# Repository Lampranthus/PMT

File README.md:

NOTAS
---
PCB

El adc tiene que llevar la siguiente configuración, solo se tenecesita por ahora un solo canal.

en esta configuración se utiliza la referencia programable del adc, con ese valor de resistencias la referncia se cambia a 1.5V segun la hora de datos.

Mientras que para recibir la señal senecesita esta configuración, solo se necesita por ahora un solo canal.

---
FPGA

QUiero usar por el momoento la DE2-115 ya que cuenta con conexiones Ethernet, voy a conectar la pcb los pines de la fpga con un socket, por el monento imagino que será mejor hacer la pcb de manera vertical respecto a la fpga, ya que por el estacio parece lo mejor.

tanbien se tienen que agregar 2 pines a la pcb de start y stop, los cuales se agregarán pero aun tengo la duda su puedo utilizar otra pcb que tengo donde utilizo el puerto hsmc de la fpga y 2 comparadores para recibir 2 señales, pero por el momento agregaré todo a una sola pcb.

---

Logré hacer una conectar la pgfa a mi laptop a 1gbs con el ejemplo de web server ahora toca cofigurar el ejemplo para loso usar la comunicación.

---

Para no depender del nios2 estoy optando por utilizar el verilog-ethernet

https://github.com/alexforencich/verilog-ethernet

ya hice que funcionara el echo por lo que ahora falta modificarlo para hacer la pruebas de envio de datos de la fpga a la laptop y hacer que la computadora guarde estos datos.

---

Estos son los pasos para utilizar ese repositorio primero vas al ejemplo de la de2-115 ejecutas el siguiente comando para generar los archivos,

```bash
make
```
luego para configurar la fpga se ejecuta el siguiente comando,

```bash
make program
```
Dado que la FPGA no tiene servidor DHCP, tu PC necesita una IP fija.

```bash
sudo ip addr flush dev enxc8a362c9957b
sudo ip addr add 192.168.1.100/24 dev enxc8a362c9957b
sudo ip link set enxc8a362c9957b up
```
Reemplaza enxc8a362c9957b con el nombre real de tu interfaz Ethernet (usa ip addr para comprobar).

Ejecuntando esos comando ya se puede recibir el echo desde la fpga utilizando el comando,

```bash
echo "respuesta" | nc -u 192.168.1.128 1234
```
Cuando haces eso, netcat:

1. Abre un socket UDP.

2. Envía el mensaje a la FPGA.

3. Se queda esperando brevemente una respuesta en el mismo socket (puerto efímero).

4. Recibe la respuesta de la FPGA (que hizo eco del mensaje) y lo imprime.

5. Luego cierra el socket.

Y sí, cuando el socket no recibe más datos, tienes que presionar Ctrl+C para cerrarlo porque nc no se cierra automáticamente si está esperando más datos.

---
En el repositorio hay un codigo en python que funciona para neciar cierto numero de paquestes a la fpga y cuando esta los regrese cuenta cuantos de estos paquestes se perdieron en el loop, hice una prueba con 100 millones de packetes y el porcentaje de paquetes que se perdieron fue minima por lo que alparecer los datos dificilmente se pierden.

ahora faltaría ver la velocidad en la que los datos se envian.

---
estoy utilizando el protocolo udp, y haciendo una prueba para el limite de longitud antes de que el ejemplo de echo no respondiera llegue a 1472 bytes de payload limite.

---

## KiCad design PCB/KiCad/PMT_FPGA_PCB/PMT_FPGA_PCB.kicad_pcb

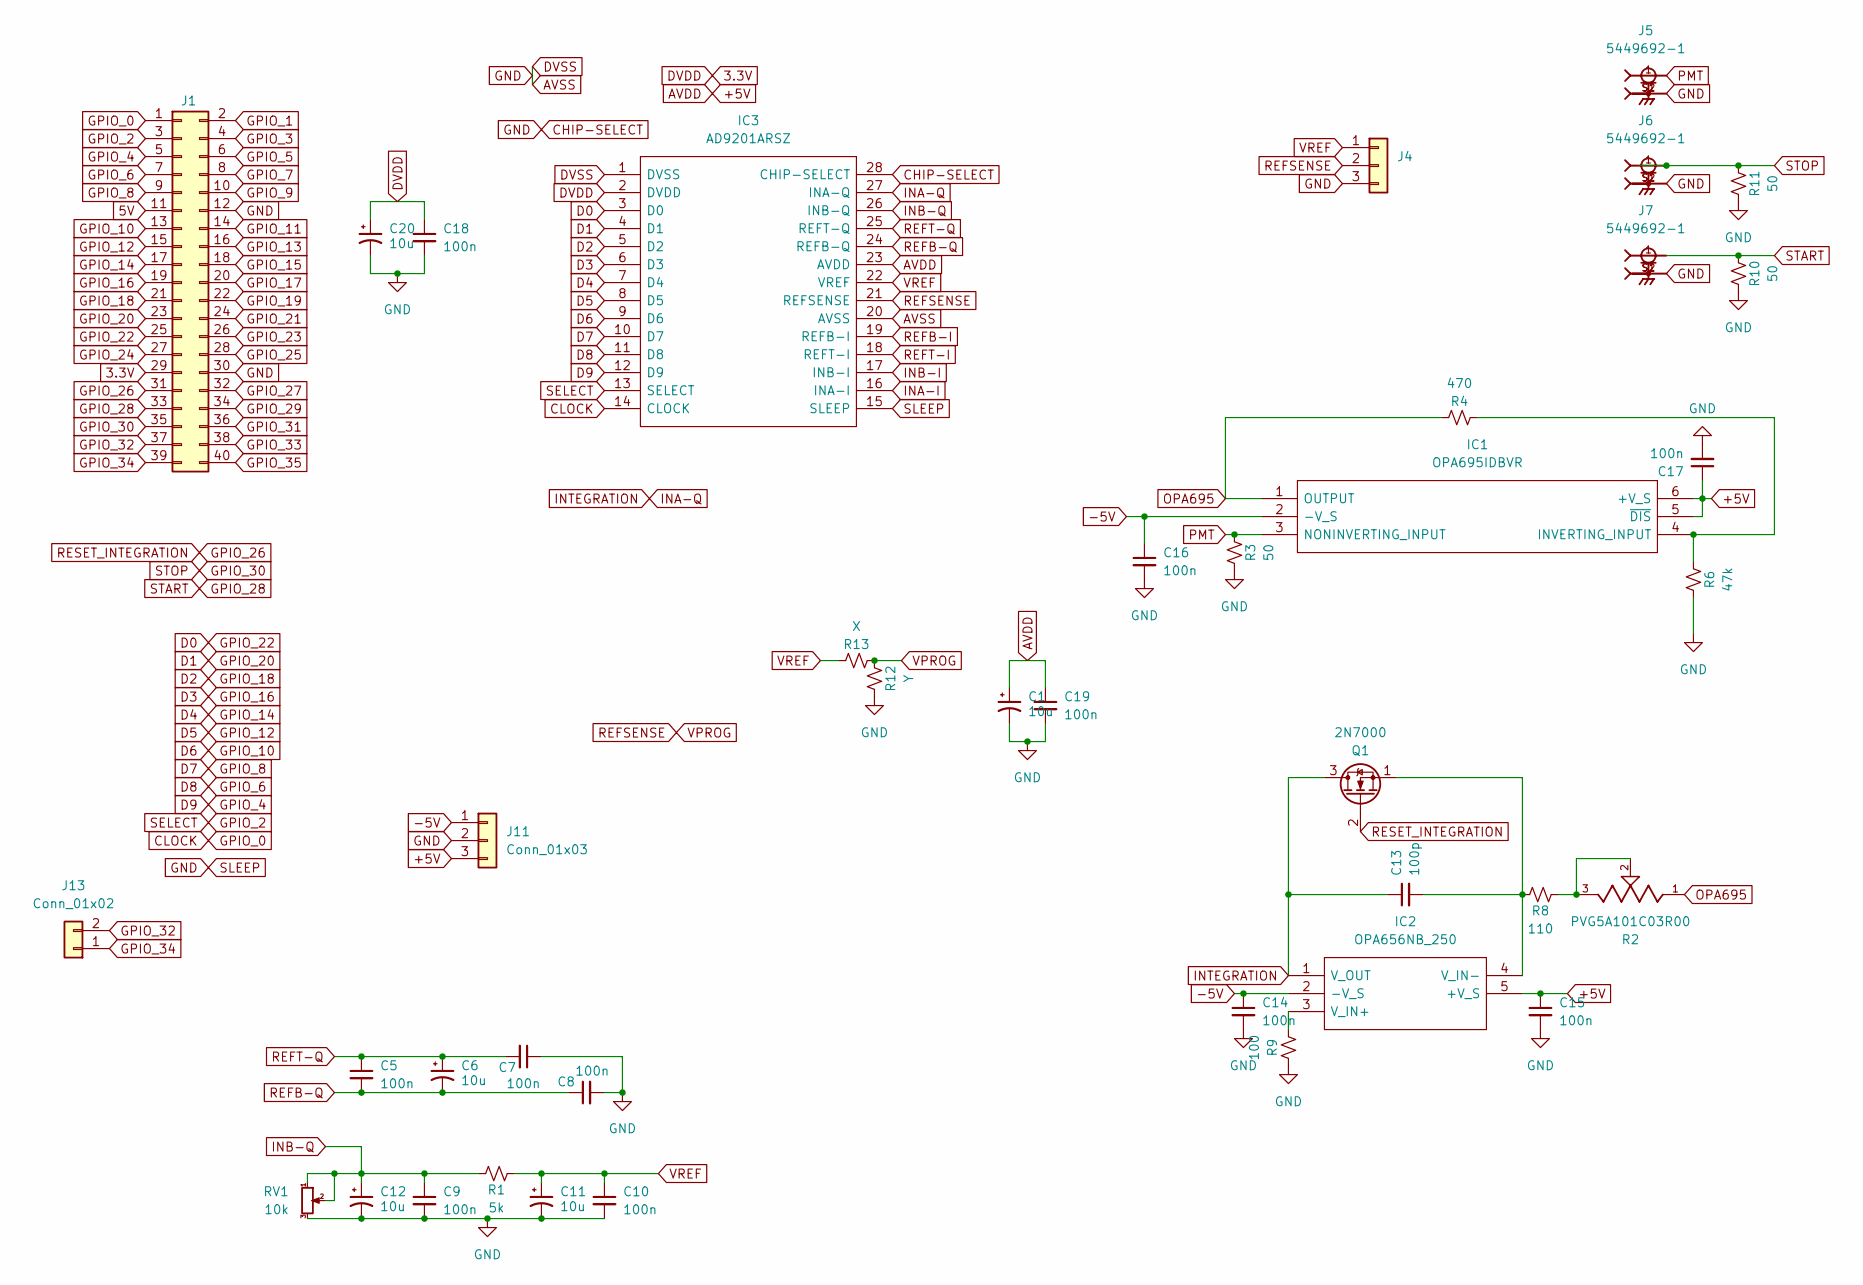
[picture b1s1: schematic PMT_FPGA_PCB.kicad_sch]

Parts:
C1, C6, C11, C12, C20: 10u; C_1206_3216Metric_Pad1.33x1.80mm_HandSolder
C5, C7, C8, C9, C10, C14, C15, C16, C17, C18, C19: 100n; C_0603_1608Metric_Pad1.08x0.95mm_HandSolder
C13: 100p; C_0603_1608Metric_Pad1.08x0.95mm_HandSolder
IC1: OPA695IDBVR; SOT95P280X145-6N; Mouser Part Number 595-OPA695IDBVR
IC2: OPA656NB_250; SOT95P280X145-5N; Mouser Part Number 595-OPA656NB/250
IC3: AD9201ARSZ; SOP65P777X198-28N; Mouser Part Number 584-AD9201ARSZ
J1: Conn_02x20_Odd_Even; PinSocket_2x20_P2.54mm_Horizontal
J4: Conn_01x03; PinHeader_1x03_P2.54mm_Vertical
J5, J6, J7: 5449692-1; TE_5449692-1; PARTREV A
J11: Conn_01x03; PinHeader_1x03_P2.54mm_Horizontal
J13: Conn_01x02; PinHeader_1x02_P2.54mm_Vertical
Q1: 2N7000; TO-92_Inline
R1: 5k; R_0805_2012Metric_Pad1.20x1.40mm_HandSolder
R2: PVG5A101C03R00; TRIM_PVG5A101C03R00; PARTREV 08/19
R3, R10, R11: 50; R_0805_2012Metric_Pad1.20x1.40mm_HandSolder
R4: 470; R_0805_2012Metric_Pad1.20x1.40mm_HandSolder
R6: 47k; R_0805_2012Metric_Pad1.20x1.40mm_HandSolder
R8: 110; R_0805_2012Metric_Pad1.20x1.40mm_HandSolder
R9: 100; R_0805_2012Metric_Pad1.20x1.40mm_HandSolder
R12: Y; R_0805_2012Metric_Pad1.20x1.40mm_HandSolder
R13: X; R_0805_2012Metric_Pad1.20x1.40mm_HandSolder
RV1: 10k; Potentiometer_Bourns_3296Y_Vertical

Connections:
3.3V: C18.1, C20.1, IC3.2 (DVDD), J1.29
5V: J1.11
+5V: C1.1, C15.1, C17.1, C19.1, IC1.5 (~DIS), IC1.6 (+V_S), IC2.5 (+V_S), IC3.23 (AVDD), J11.3
-5V: C14.1, C16.1, IC1.2 (-V_S), IC2.2 (-V_S), J11.1
AVSS: C1.2, C7.1, C8.2, C9.2, C10.2, C11.2, C12.2, C14.2, C15.2, C16.2, C17.2, C18.2, C19.2, C20.2, IC3.1 (DVSS), IC3.15 (SLEEP), IC3.20 (AVSS), IC3.28 (CHIP-SELECT), J1.12, J1.30, J4.3, J5.S1, J5.S2, J6.S1, J6.S2, J7.S1, J7.S2, J11.2, R3.1, R6.1, R9.2, R10.1, R11.1, R12.1, RV1.3
CLOCK: IC3.14 (CLOCK), J1.1
D0: IC3.3 (D0), J1.25
D1: IC3.4 (D1), J1.23
D2: IC3.5 (D2), J1.21
D3: IC3.6 (D3), J1.19
D4: IC3.7 (D4), J1.17
D5: IC3.8 (D5), J1.15
D6: IC3.9 (D6), J1.13
D7: IC3.10 (D7), J1.9
D8: IC3.11 (D8), J1.7
D9: IC3.12 (D9), J1.5
GPIO_1: J1.2
GPIO_2: IC3.13 (SELECT), J1.3
GPIO_3: J1.4
GPIO_5: J1.6
GPIO_7: J1.8
GPIO_9: J1.10
GPIO_11: J1.14
GPIO_13: J1.16
GPIO_15: J1.18
GPIO_17: J1.20
GPIO_19: J1.22
GPIO_21: J1.24
GPIO_23: J1.26
GPIO_24: J1.27
GPIO_25: J1.28
GPIO_26: J1.31, Q1.2 (G)
GPIO_27: J1.32
GPIO_28: J1.33, J7.1, R10.2
GPIO_29: J1.34
GPIO_30: J1.35, J6.1, R11.2
GPIO_31: J1.36
GPIO_32: J1.37, J13.2
GPIO_33: J1.38
GPIO_34: J1.39, J13.1
GPIO_35: J1.40
INA-I: IC3.16 (INA-I)
INA-Q: C13.1, IC2.1 (V_OUT), IC3.27 (INA-Q), Q1.3 (D)
INB-I: IC3.17 (INB-I)
INB-Q: C9.1, C12.1, IC3.26 (INB-Q), R1.1, RV1.1, RV1.2
unnamed: IC1.4 (INVERTING_INPUT), R4.1, R6.2
unnamed: IC2.3 (V_IN+), R9.1
unnamed: C13.2, IC2.4 (V_IN-), Q1.1 (S), R8.1
unnamed: R2.2, R2.3, R8.2
OPA695: IC1.1 (OUTPUT), R2.1, R4.2
PMT: IC1.3 (NONINVERTING_INPUT), J5.1, R3.2
REFB-I: IC3.19 (REFB-I)
REFB-Q: C5.2, C6.2, C8.1, IC3.24 (REFB-Q)
REFSENSE: IC3.21 (REFSENSE), J4.2, R12.2, R13.1
REFT-I: IC3.18 (REFT-I)
REFT-Q: C5.1, C6.1, C7.2, IC3.25 (REFT-Q)
VREF: C10.1, C11.1, IC3.22 (VREF), J4.1, R1.2, R13.2

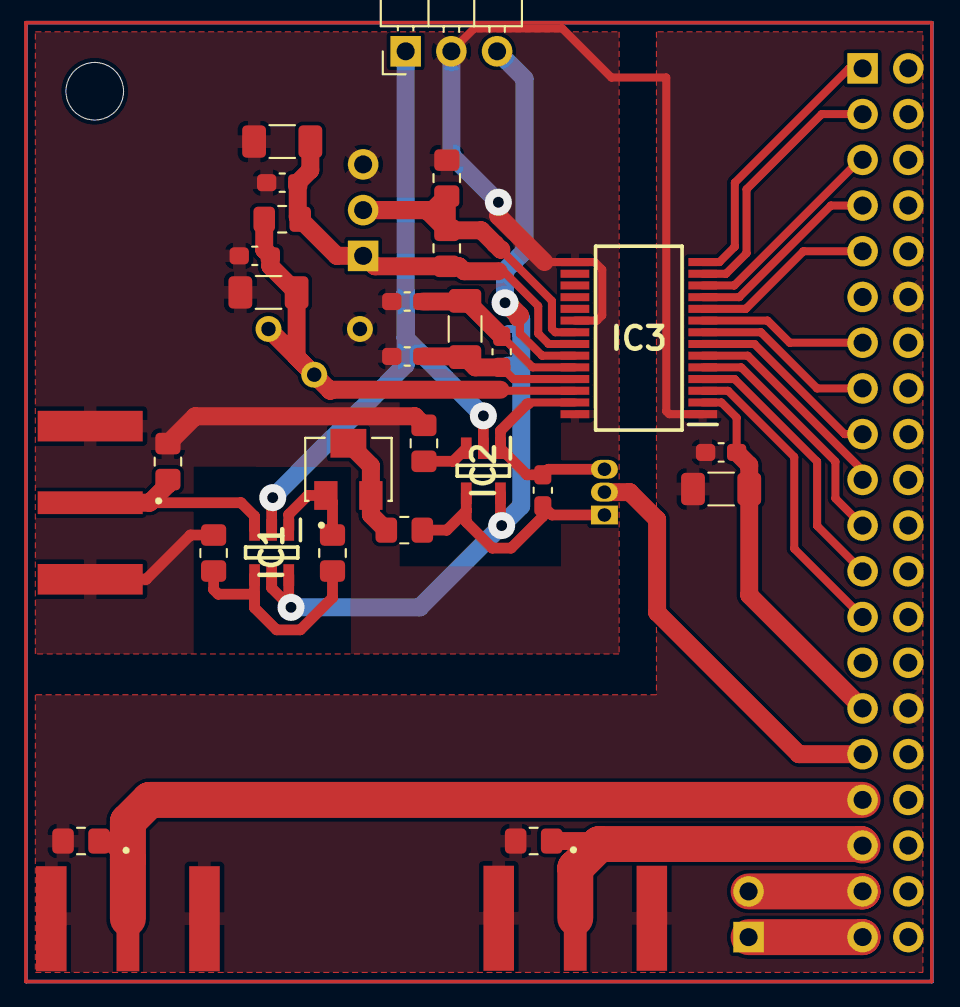
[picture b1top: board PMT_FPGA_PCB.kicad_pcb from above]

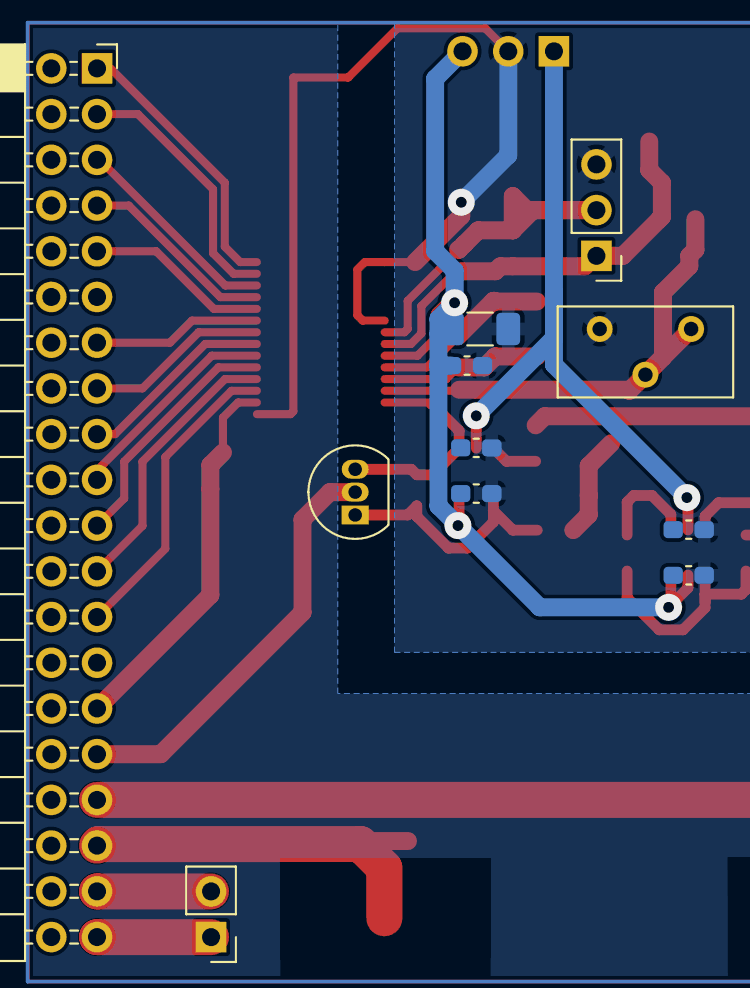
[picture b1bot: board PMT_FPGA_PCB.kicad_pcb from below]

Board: 2 copper layers, 40 parts (11 on the bottom side), 33 nets.

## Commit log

2025-05-14 Ethenet added
2025-06-02 firmware ok
2025-06-02 firmware ok ok
2025-06-04 firmware adc-ethernet
2025-06-04 firmware adc-ethernet se pierden datos
2025-06-04 software udp sniffer ok
2025-06-06 software datos casi ok revisar tiempos
2025-06-07 software adc ok 125mhz, pendiente axi fifo
2025-06-07 software adc ok 125mhz udp ok, pendiente registro paralelo
2025-06-07 creando imagen
2025-06-11 software ok, pendiente revisar memorias
2025-06-12 software ok, pendiente registro y ploteo
2025-06-12 version 1 ok
